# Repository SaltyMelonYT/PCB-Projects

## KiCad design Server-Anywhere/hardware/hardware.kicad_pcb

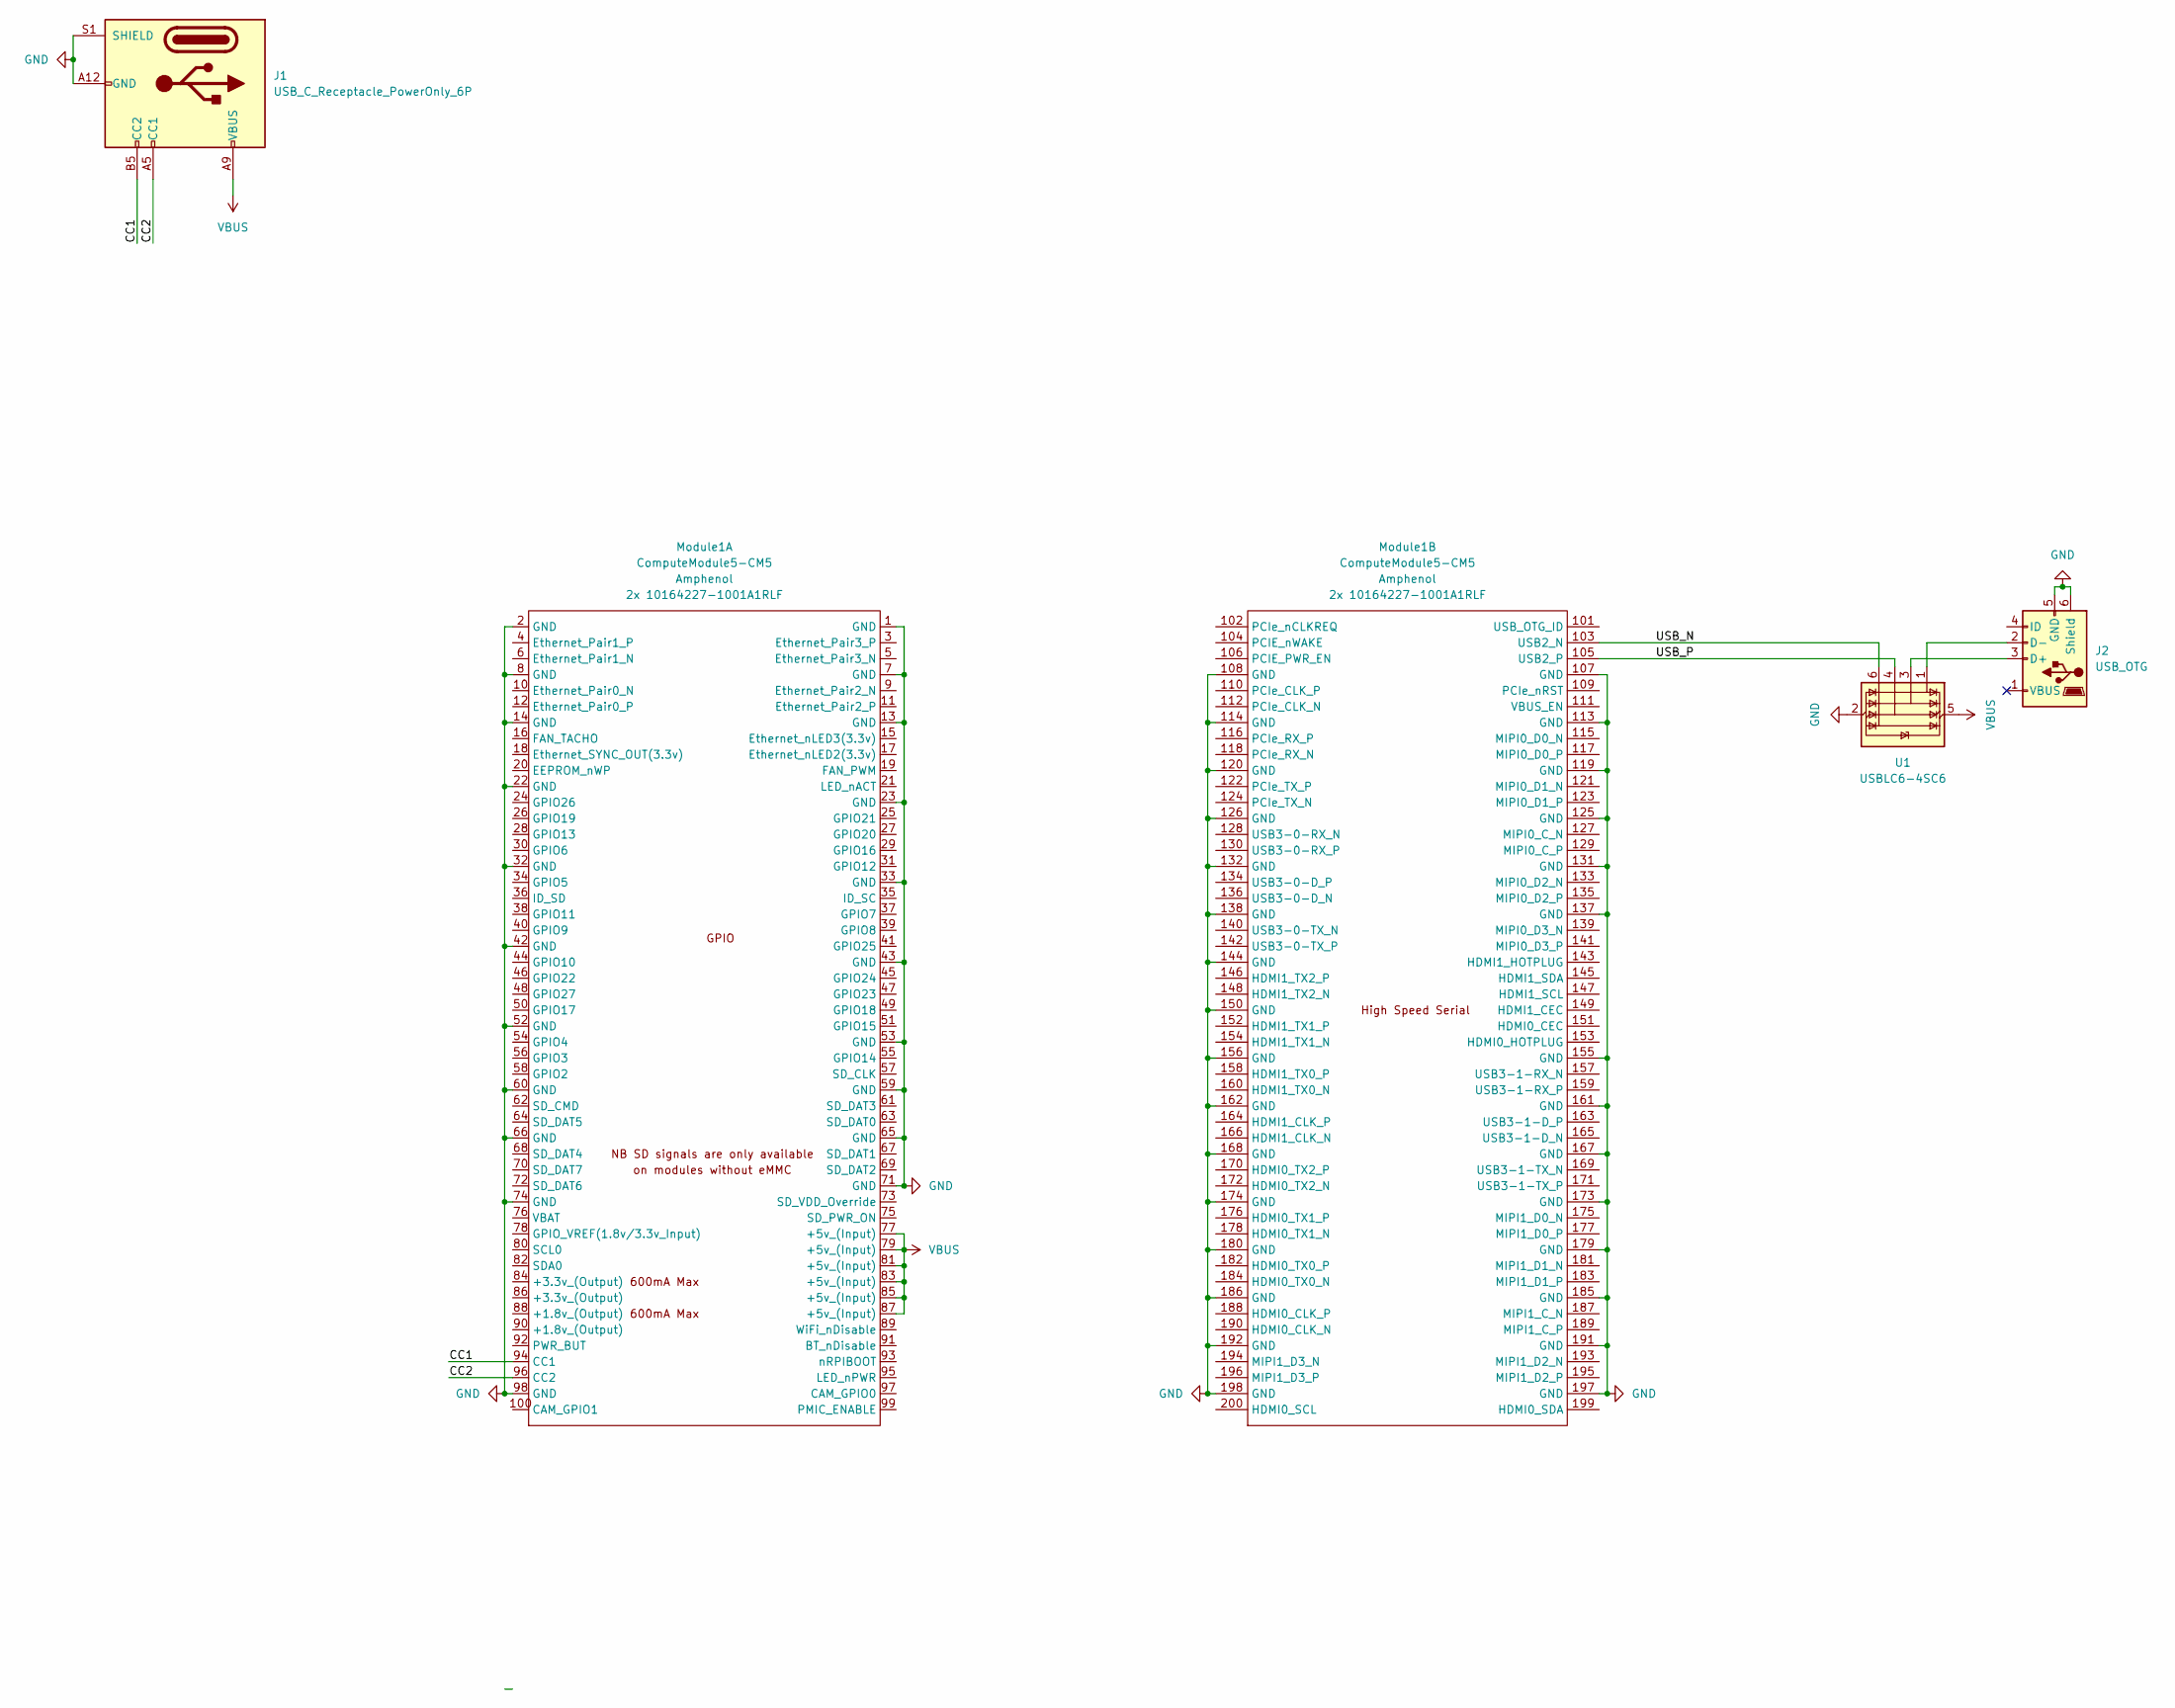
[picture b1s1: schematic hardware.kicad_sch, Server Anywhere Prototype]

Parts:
J1: USB_C_Receptacle_PowerOnly_6P; USB_C_Receptacle_GCT_USB4125-xx-x-0190_6P_TopMnt_Horizontal
J2: USB_OTG; USB_Micro-B_Amphenol_10103594-0001LF_Horizontal
Module1: ComputeModule5-CM5; Raspberry-Pi-5-Compute-Module
U1: USBLC6-4SC6; SOT-23-6

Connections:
/CC1: J1.B5 (CC2), Module1.94 (CC1)
/CC2: J1.A5 (CC1), Module1.96 (CC2)
/USB_N: Module1.103 (USB2_N), U1.6 (I/O4)
/USB_P: Module1.105 (USB2_P), U1.4 (I/O3)
GND: J1.A12 (GND), J1.B12 (GND), J1.S1 (SHIELD), J2.5 (GND), J2.6 (Shield), Module1.1 (GND), Module1.2 (GND), Module1.7 (GND), Module1.8 (GND), Module1.13 (GND), Module1.14 (GND), Module1.22 (GND), Module1.23 (GND), Module1.32 (GND), Module1.33 (GND), Module1.42 (GND), Module1.43 (GND), Module1.52 (GND), Module1.53 (GND), Module1.59 (GND), Module1.60 (GND), Module1.65 (GND), Module1.66 (GND), Module1.71 (GND), Module1.74 (GND), Module1.98 (GND), Module1.107 (GND), Module1.108 (GND), Module1.113 (GND), Module1.114 (GND), Module1.119 (GND), Module1.120 (GND), Module1.125 (GND), Module1.126 (GND), Module1.131 (GND), Module1.132 (GND), Module1.137 (GND), Module1.138 (GND), Module1.144 (GND), Module1.150 (GND), Module1.155 (GND), Module1.156 (GND), Module1.161 (GND), Module1.162 (GND), Module1.167 (GND), Module1.168 (GND), Module1.173 (GND), Module1.174 (GND), Module1.179 (GND), Module1.180 (GND), Module1.185 (GND), Module1.186 (GND), Module1.191 (GND), Module1.192 (GND), Module1.197 (GND), Module1.198 (GND), U1.2 (GND)
unnamed: J2.3 (D+), U1.3 (I/O2)
unnamed: J2.2 (D-), U1.1 (I/O1)
VBUS: J1.A9 (VBUS), J1.B9 (VBUS), Module1.77 (+5v_(Input)), Module1.79 (+5v_(Input)), Module1.81 (+5v_(Input)), Module1.83 (+5v_(Input)), Module1.85 (+5v_(Input)), Module1.87 (+5v_(Input)), U1.5 (VBUS)

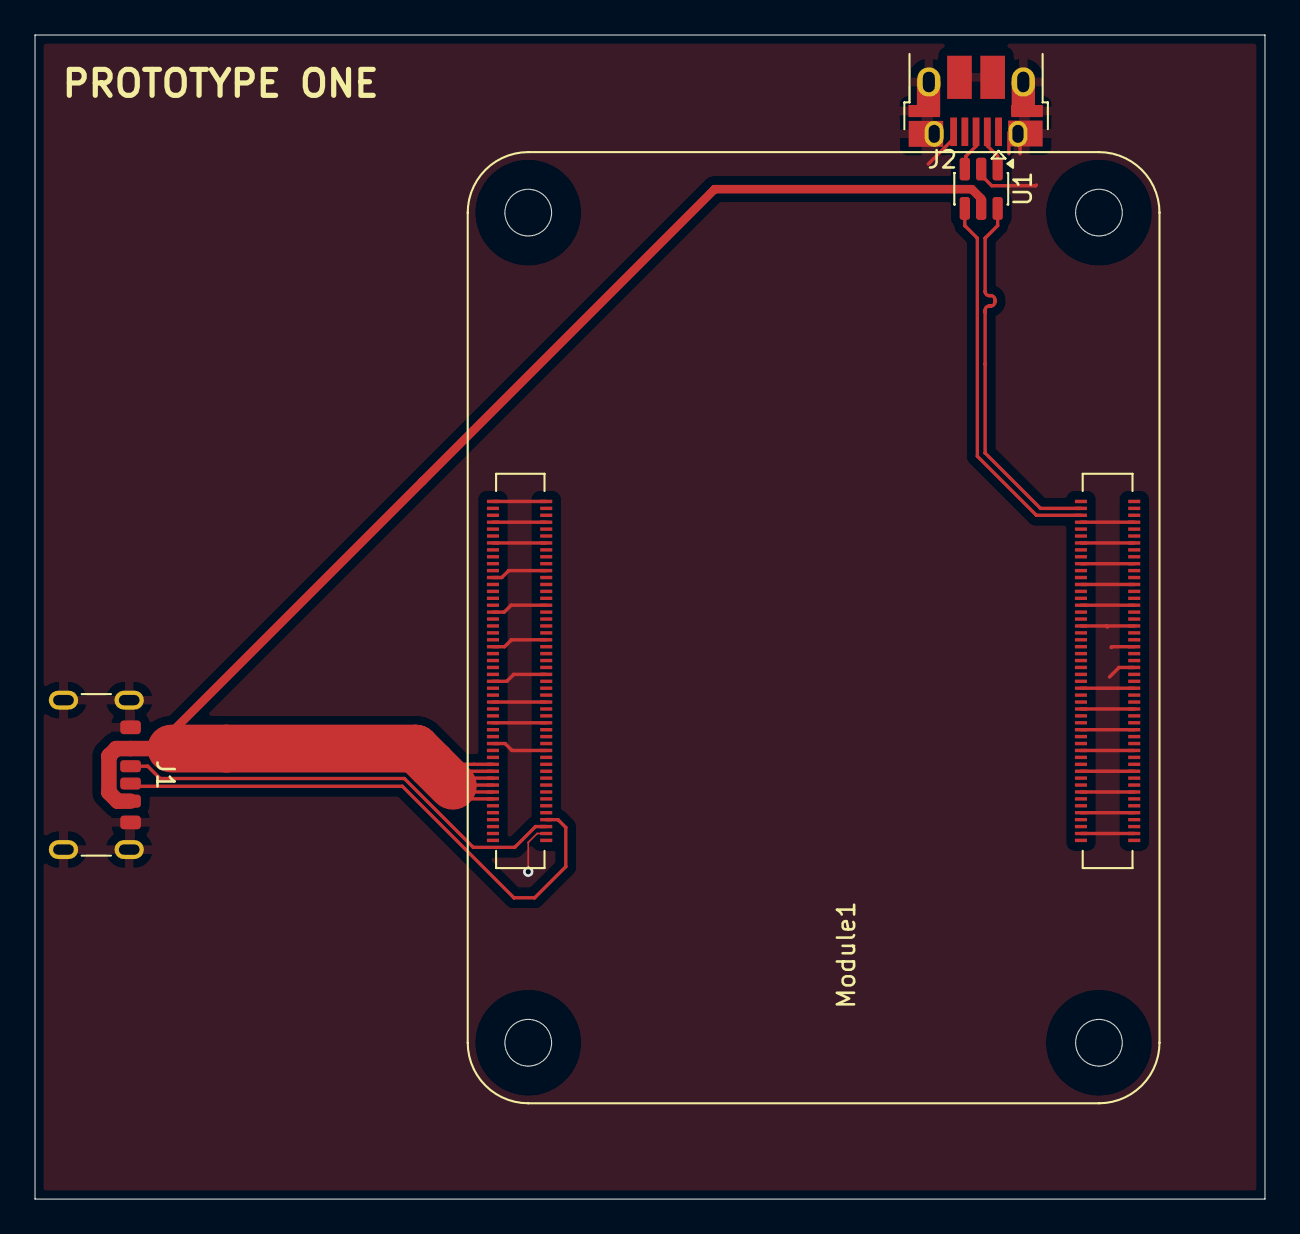
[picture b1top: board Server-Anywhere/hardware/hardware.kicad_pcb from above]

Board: 2 copper layers, 71.1 x 67.3 mm, 4 parts (0 on the bottom side), 8 nets.

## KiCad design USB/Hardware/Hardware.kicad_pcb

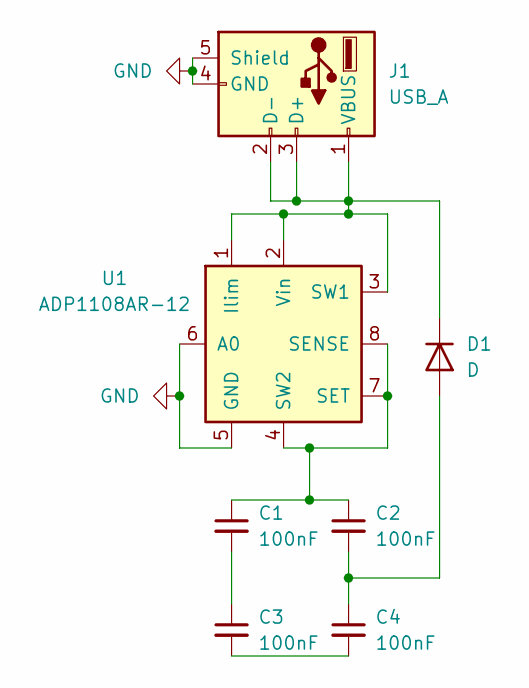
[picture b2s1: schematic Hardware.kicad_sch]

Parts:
C1, C2, C3, C4: 100nF; C_0201_0603Metric_Pad0.64x0.40mm_HandSolder
D1: D; D_0402_1005Metric_Pad0.77x0.64mm_HandSolder
J1: USB_A; USB_A_Receptacle_GCT_USB1046
U1: ADP1108AR-12; SOIC-8_3.9x4.9mm_P1.27mm

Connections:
GND: J1.4 (GND), J1.5 (Shield), U1.5 (GND), U1.6 (A0)
unnamed: C1.2, C3.1
unnamed: C3.2, C4.2
unnamed: C2.2, C4.1, D1.2 (A)
unnamed: D1.1 (K), J1.1 (VBUS), J1.2 (D-), J1.3 (D+), U1.1 (Ilim), U1.2 (Vin), U1.3 (SW1)
unnamed: C1.1, C2.1, U1.4 (SW2), U1.7 (SET), U1.8 (SENSE)

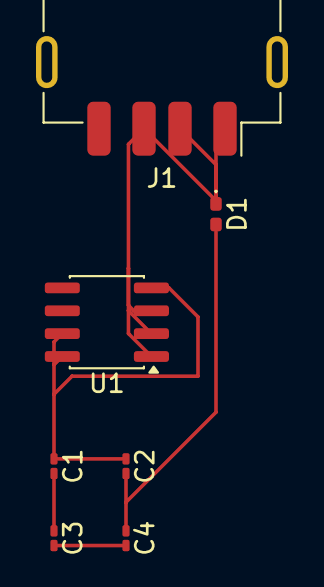
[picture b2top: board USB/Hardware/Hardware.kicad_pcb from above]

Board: 2 copper layers, 7 parts (0 on the bottom side), 6 nets.
